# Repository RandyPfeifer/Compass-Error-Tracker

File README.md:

# Compass-Error-Tracker
Using a compass, GPS and small display, plot accumulated error (+/-) in your heading vs intended course

This project was undertaken to provide training experiences for canoe paddlers interested in improving their ability to paddle from Point A 
directly to Point B when they know the initial direction to B while sitting at A. It can also be used in the field when paddling in circumstances where 
visibility is impaired (i.e., fog) and a target is not readily visible while enroute.

The second purpose of this project was as a learning experience for myself as this is my first Arduino, MC5883L, SSD1306, NEO-6M and Github experience. 

The project utilized an Arduino compatible processor with I2C services to communicate with a MC5883L compass module to measure changes in direction 
as well as a SSD1306-based 128 x 64 pixel display to output onoing assessment of accumulated error.  The GPS module in play is the NEO-6M module using software serial for UART communication.Two specfic processors have been tested with this software:  Arduino Nano Every and Seeeduino XIAO.  The Nano was used during early development but most all testing and later development (GPS in particular) was done on the Seeeduino XIAO. 

When initialized (on power-up or reset or when the push_button is released), the system samples the immediate / current direction the craft is pointing (don't turn the system on until you are pointing where you want to go).  Note that all compass measurements taken are actually an average of 3 samples taken 300 ms apart to remove a bit of noise.  This bearing formed from 9 samples (3 reads of 3 samples each averaged) is then used as the intended (target) course.  The display will signal "TARGET ACQUIRED" when this is accomplished. 

Subsequent measurements on a periodic basis (2 - 3 seconds) are compared with the initially recorded target course.  
If a measurement is different from the initally captured target, that "Error" is displayed in the middle of the screen and accumulated with subsequent measurements.  
The accumulated error may grow or shrink depending on adjustments made by the person steering the craft. Ideally
they would strive to keep this accumulated error as small as possible without resorting to abrupt changes in direction (no sudden moves).

The overall accumulated Error (degree - seconds) is displayed graphically as a growing (or shrinking) 1/4 circle. The sign (+/-) of this accumulated
error is conveyed by which half of the screen the 1/4 circle is placed:

- 1/4 circle on right indicates the accumulated error has moved the craft to the right of intended course.
- 1/4 circle on the left indicates an accumulated error moving to the left of the intended course.

As the accumulated error grows or shrinks the radius of the 1/4 circle expands or contracts. As you move from the accumulated error being positive to negative, 
the 1/4 circle of interest flips to the other side of the display.

The intent would be for the user to adjust their steering to keep the circle radius as small as possible (ideally near zero). 

If the accumulated error grows beyond a defined threshold, the screen is updated to add a "turn signal" to the blank side of the screen.  For example, if the craft has strayed off to the right and a large 1/4 circle has grown on the right side of the screen, the left side of the screen will display a left turn signal.  Similarly for the opposite condition.  

Also, if the accumulated error grows beyond a certain (larger) threshold, the current cycle measured error number is displayed in Yellow and large Font to signal the need for more aggressive action to correct the error.

Further, if the accumulated error grows to an enormous threshold, the side of the screen reflecting that error will display the actual accumulated error to be "worked off" by steering in the appropriate direction indicated on the other side of the display. 

At any time, the button on the unit can be pressed which will effectively restart the process, taking a new target bearing and zeroing out the accumulated error. 

A short video of the program in operation (inside my house) can be found here:  https://youtu.be/wzSbLun69U0

## Notes

This system is unaware of effects of wind on the craft in motion.  As such, on windy days, "off course" conditions can be experienced even
if the accumulated error is maintained at zero. 

Similarly, this system is unaware of the speed of the craft and assumes a constant speed. 

Under the conditions of no wind (or other forces that would move the craft off course), and a constant speed, the display will provide a faithful indication of on/off course and a relative magnitued of the current off-course condition. 

There is some  code in there to account for the 32bit vs 16 bit differences between the processors and the fact that the measured samples from the compass module are 16 bit signed integers.

Schematic and board designs included in /src (created with Autodesk - Eagle).
A few pictures in /Examples. including a photo of a hand etched board and first assembled prototype and a link to a utube video of working system.

## GPS services

The unit also includes a GPS module.  Once it is in service and has a lock with a sufficient number of satellites, it will begin to deliver NMEA sentences with location (lat/lon), heading, speed, etc.  The software will switch to navigating using the GPS once certain criteria are met:

1. The paddler is within a certain cumulative error level (we want them to be close to their original intended line of travel)
2. The current heading is close to the intended heading identified at the beginning of the session (i.e., pointing in the right direction)

These criteria ensure that the craft is on the correct path (ignoring wind conditions referenced above) and GPS navigation can continue from there. 
After maintaining this criteria for a period of about 45 seconds, the GPS will derive a heading from its own readings and determine the heading target that the GPS will follow.
This avoids the need for the compass to produce a heading that is true to the real world (we only needed relative changes in direction from the compass to do all of our navigation so far). 

With that GPS-derived heading the software calculates the deviation from a line drawn from the point the GPS came into service (point A') in the direction of the GPS-derived target heading.  This deviation is now displayed as the cumulative error in the same fashion cumulative errors were displayed under compass navigation. The error displayed in the middle of the screen, which used to be the difference in current compass angle and the intended heading, is replaced with a new error which is the difference in current heading and the intended heading. Hence the meaning and interpretation of the display are consistent in Compass and GPS modes. 

In the upper right corner of the display will be an indicator of the status of the GPS module:
- !G - no GPS services are available
- ~G - the system is currently using valid GPS data and is in the 45+ second training cycle with the above criteria being met (this cycle may fail and need to be extended until the above criteria are met again - a flip back to !G).
- G! - the system has acheived all criteria for switching to GPS navigation and has made the transition. No further us of the compass is needed. 

When G! has been acheived, the upper left corner of the display shows the current heading reported by the GPS. 

Every 2-3 seconds, the GPS is polled for new information and the error calculation is repeated and the display updated.  The paddler can now be confident that no additional error can be introduced by effects of wind or current.  As long as GPS services remain, the system will continue to deliver accurate assessment of the overall divergence from the GPS derived heading.  

In order to eliminate any error in the GPS training cycle, the user can choose to explicitly provide the intended heading (in addition to pointing the craft in the proper direction when the system is powered up).   Even if GPS services are not available, the user can press the (reset) button on the unit and hold it down for an excess of 3 seconds.  This will signal the system to enter an "input" mode and it will display the current compass reading on the display.  The user can then rotate the unit to get the compass direction they are intending to travel on the display.  Once this is acheived, simply releasing the button will cause this last reading to be recorded for future use by the GPS.  Once the GPS comes online, the training process is circumvented and the system begins to immediatley navigate using the "input" target heading. 

The user could of course wait at their starting point for the GPS to be in service and perform all of their paddling under the guidance of the GPS.

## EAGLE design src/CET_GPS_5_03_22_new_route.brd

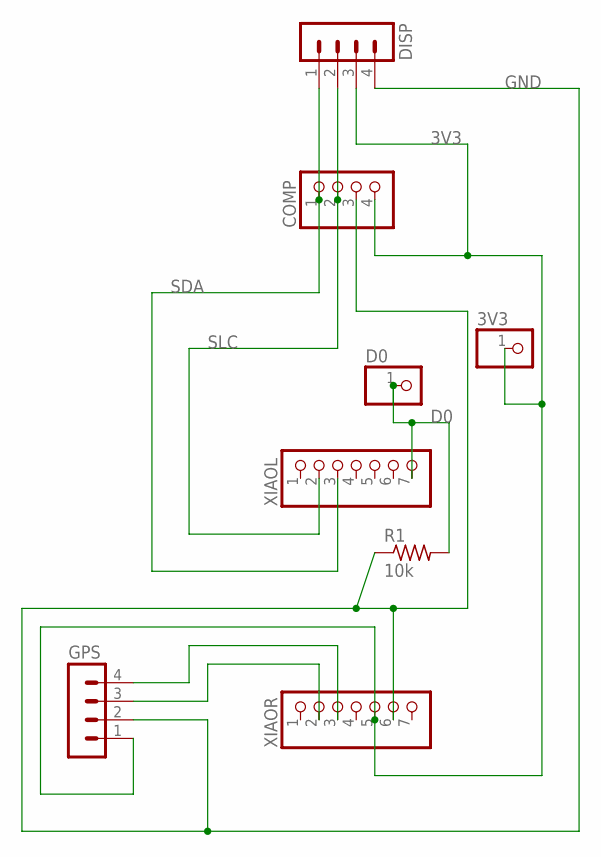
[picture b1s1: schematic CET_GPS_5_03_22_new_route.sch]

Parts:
3V3: PINHD-1X1; 1X01
COMP: PINHD-1X4/90; 1X04/90
D0: PINHD-1X1; 1X01
DISP: MA04-1
GPS: MA04-1
R1: 10k; 0204/7
XIAOL: PINHD-1X7; 1X07
XIAOR: PINHD-1X7; 1X07

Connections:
3V3: 3V3.1, COMP.4, DISP.3, GPS.1, XIAOR.5
D0: D0.1, R1.2, XIAOL.7
GND: COMP.3, DISP.4, GPS.2, R1.1, XIAOR.6
RX: GPS.3, XIAOR.2
SDA: COMP.1, DISP.1, XIAOL.3
SLC: COMP.2, DISP.2, XIAOL.2
TX: GPS.4, XIAOR.3

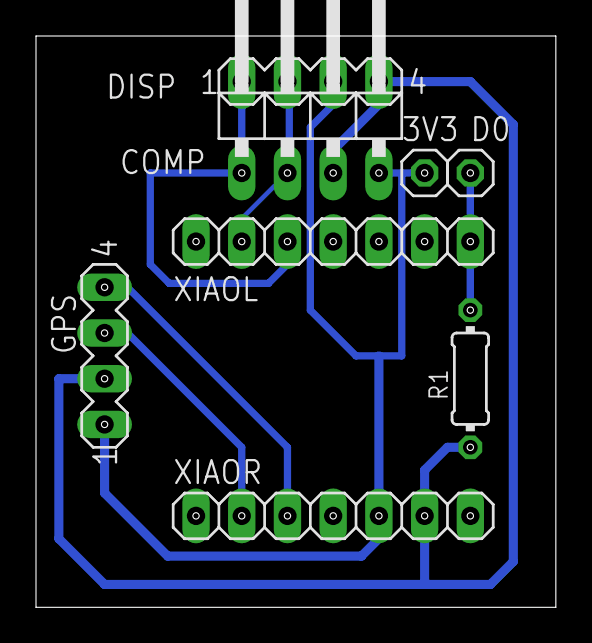
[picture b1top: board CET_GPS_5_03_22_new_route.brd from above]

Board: 2 copper layers, 28.9 x 31.7 mm, 8 parts (0 on the bottom side), 7 nets.

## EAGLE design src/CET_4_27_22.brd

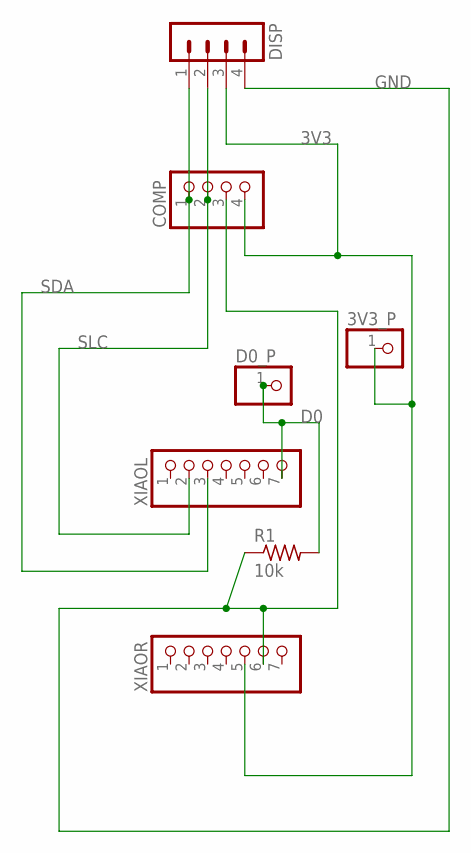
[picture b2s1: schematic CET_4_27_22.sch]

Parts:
3V3_P: PINHD-1X1; 1X01
COMP: PINHD-1X4/90; 1X04/90
D0_P: PINHD-1X1; 1X01
DISP: MA04-1
R1: 10k; 0204/7
XIAOL: PINHD-1X7; 1X07
XIAOR: PINHD-1X7; 1X07

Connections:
3V3: 3V3_P.1, COMP.4, DISP.3, XIAOR.5
D0: D0_P.1, R1.2, XIAOL.7
GND: COMP.3, DISP.4, R1.1, XIAOR.6
SDA: COMP.1, DISP.1, XIAOL.3
SLC: COMP.2, DISP.2, XIAOL.2

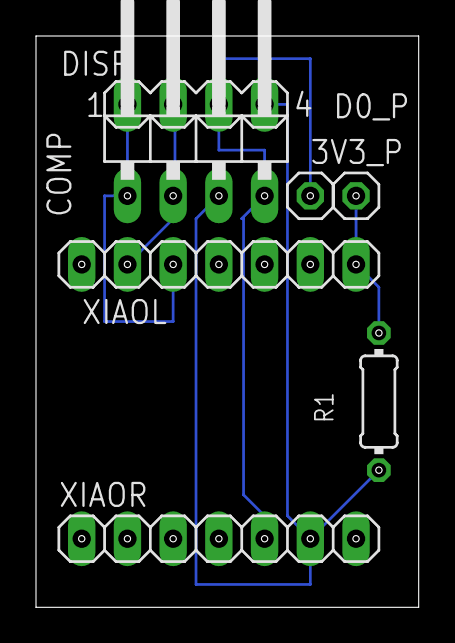
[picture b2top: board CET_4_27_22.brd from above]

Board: 2 copper layers, 21.3 x 31.7 mm, 7 parts (0 on the bottom side), 5 nets.

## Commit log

2022-04-21 Create src
2022-04-21 Create CanoeCompassErrorManager_with_display
2022-04-23 Create short video
2022-04-30 Create Contributor Covenant Code of Conduct
2022-05-06 Create CET+GPS-WIP.cpp
    Work in progress for a version of CET with GPS assist.
2022-05-10 Update LICENSE
2022-06-04 Rename CET+GPS-WIP.cpp to CET+GPS.cpp
